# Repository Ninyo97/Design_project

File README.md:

# Design_project
There are 2 Schematic files.

Sensor_post.sch
Train_module.sch

you have to create the Sensor_post.brd with following specs:
dimension: 10 x 4-5 cm^2

and the Train_module.sch with following specs:
dimension: 10 x 6-5 cm^2

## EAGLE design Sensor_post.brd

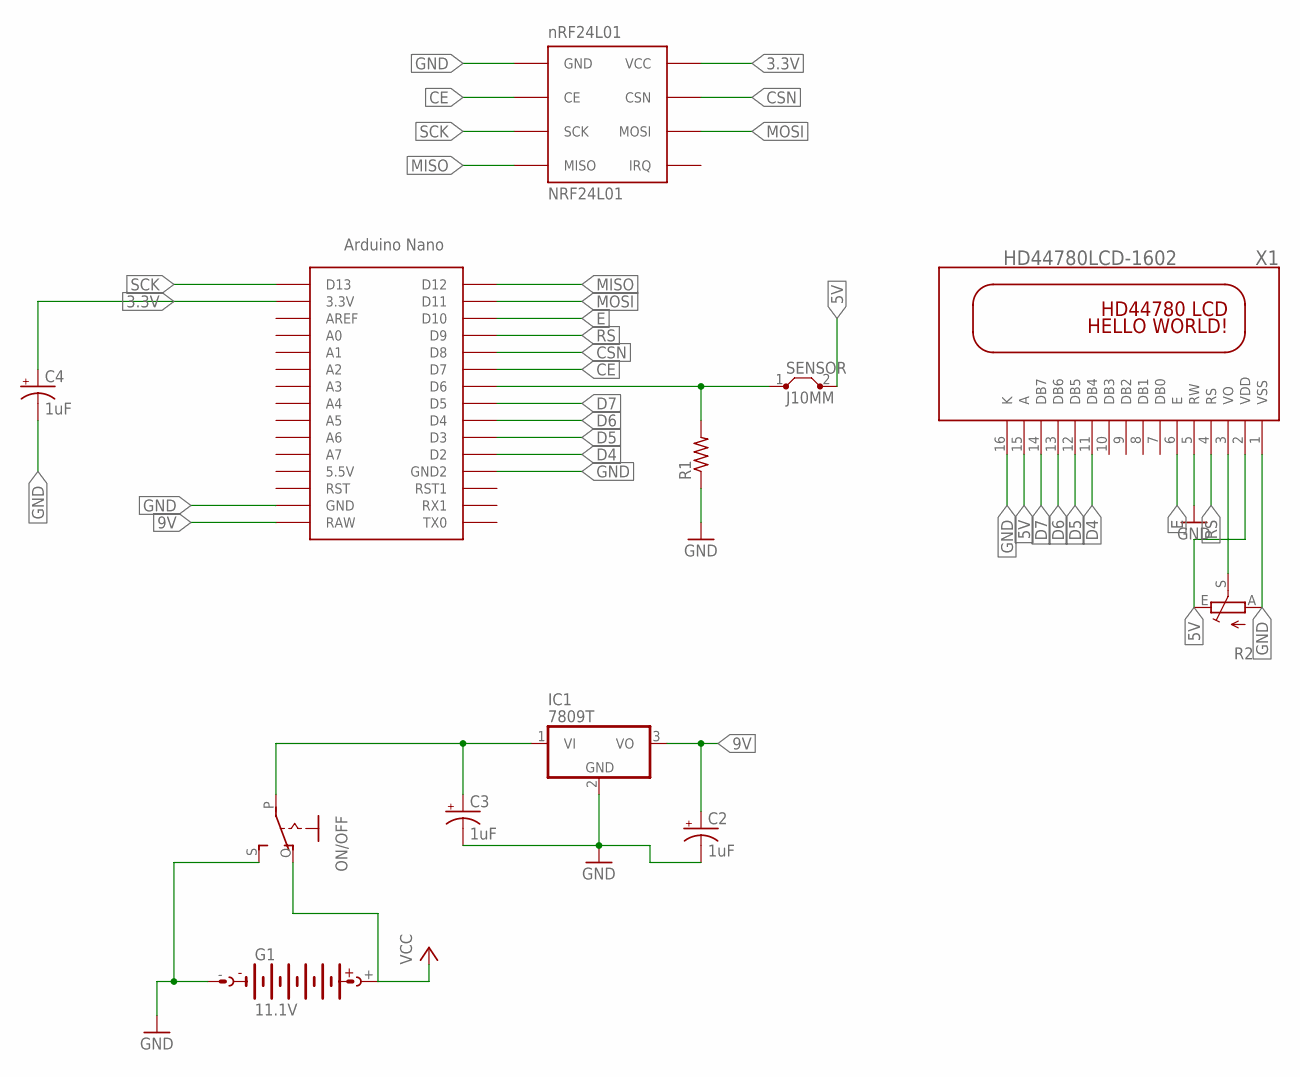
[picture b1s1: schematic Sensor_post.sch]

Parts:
C2, C3, C4: 1uF; E2,5-7
G1: 11.1V; AB9V
IC1: 7809T; TO220V
NRF24L1: NRF24L01
ON/OFF: EG1218S; EG1218
R1: R-US_0207/10; 0207/10
R2: TRIM_EU-CA9V; CA9V
SENSOR: J10MM; 10
U$1: NANO
X1: HD44780LCD-1602; LCD1602

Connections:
3.3V: C4.+, NRF24L1.VCC, U$1.3.3V
5V: R2.E, SENSOR.2, U$1.5V (5.5V), X1.2 (VDD), X1.15 (A)
9V: C2.+, IC1.3 (VO), U$1.RAW
CE: NRF24L1.CE, U$1.D7
CSN: NRF24L1.CSN, U$1.D8
D4: U$1.D2, X1.11 (DB4)
D5: U$1.D3, X1.12 (DB5)
D6: U$1.D4, X1.13 (DB6)
D7: U$1.D5, X1.14 (DB7)
E: U$1.D10, X1.6 (E)
GND: C2.-, C3.-, C4.-, G1.-, IC1.2 (GND), NRF24L1.GND, ON/OFF.S, R1.1, R2.A, U$1.GND, U$1.GND1 (GND2), X1.1 (VSS), X1.5 (RW), X1.16 (K)
MISO: NRF24L1.MISO, U$1.D12
MOSI: NRF24L1.MOSI, U$1.D11
unnamed: C3.+, IC1.1 (VI), ON/OFF.P
unnamed: R1.2, SENSOR.1, U$1.D6
unnamed: R2.S, X1.3 (VO)
RS: U$1.D9, X1.4 (RS)
SCK: NRF24L1.SCK, U$1.D13
VCC: G1.+, ON/OFF.O

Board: 2 copper layers, 12 parts (0 on the bottom side), 19 nets, no tracks yet.
